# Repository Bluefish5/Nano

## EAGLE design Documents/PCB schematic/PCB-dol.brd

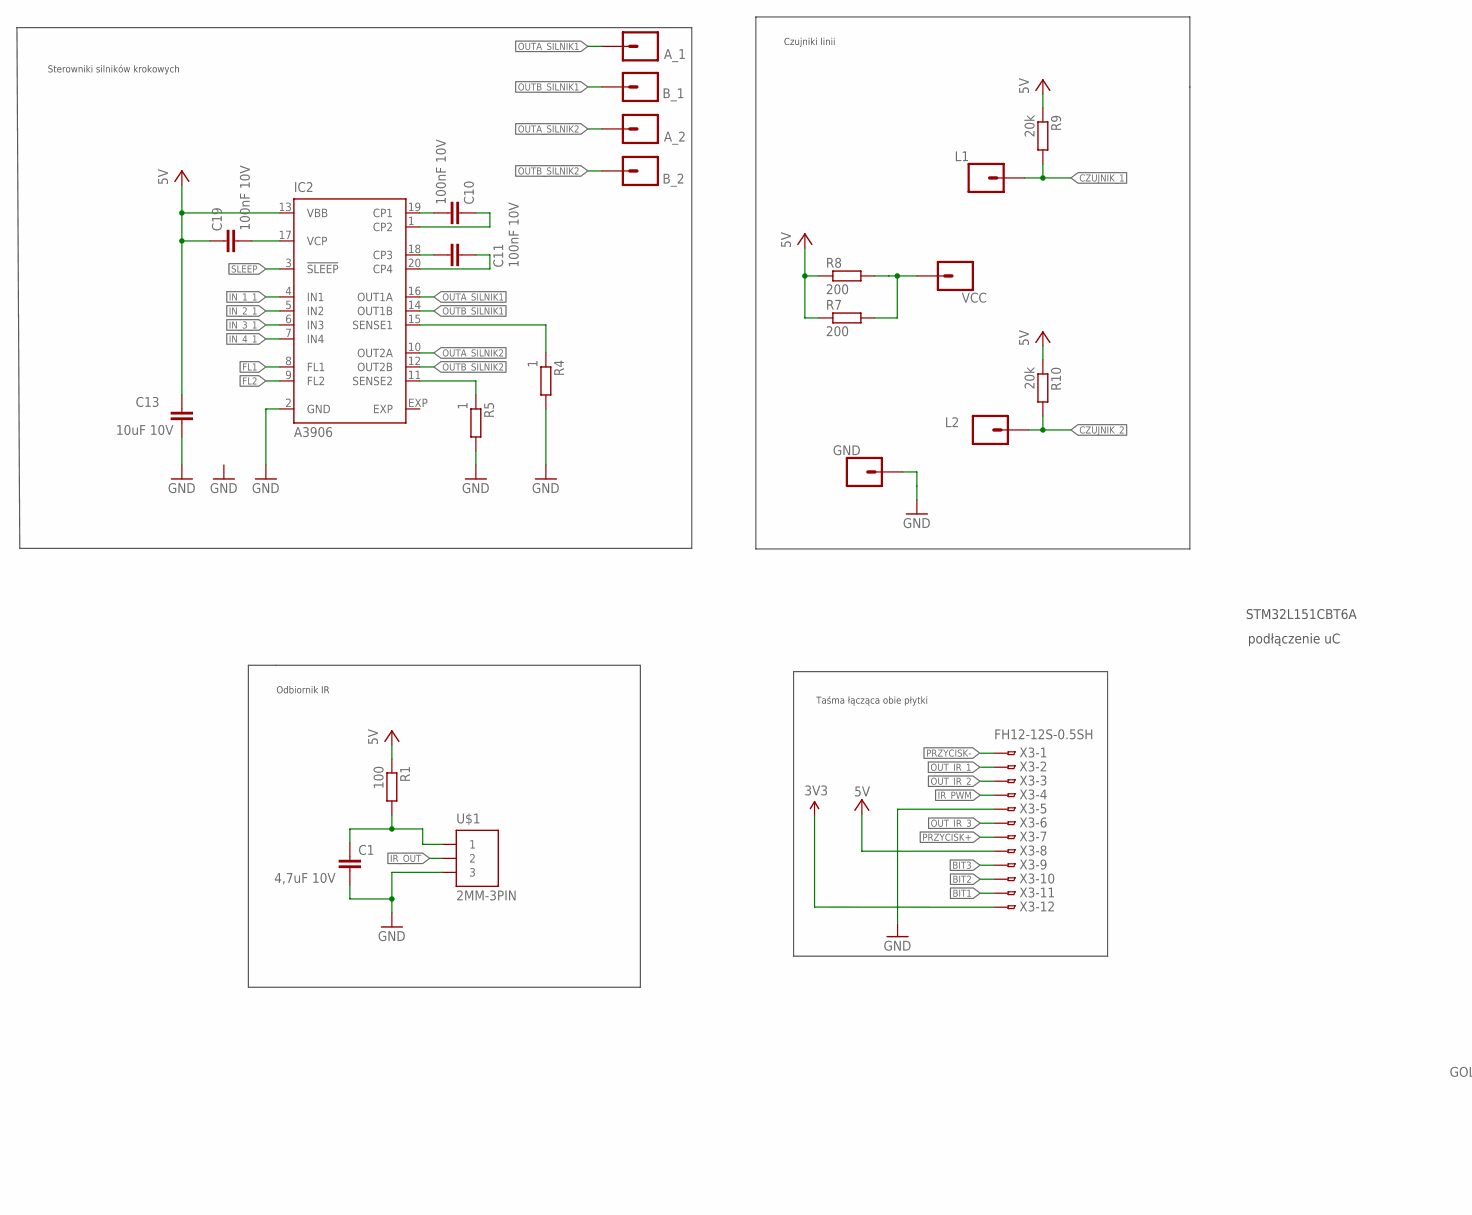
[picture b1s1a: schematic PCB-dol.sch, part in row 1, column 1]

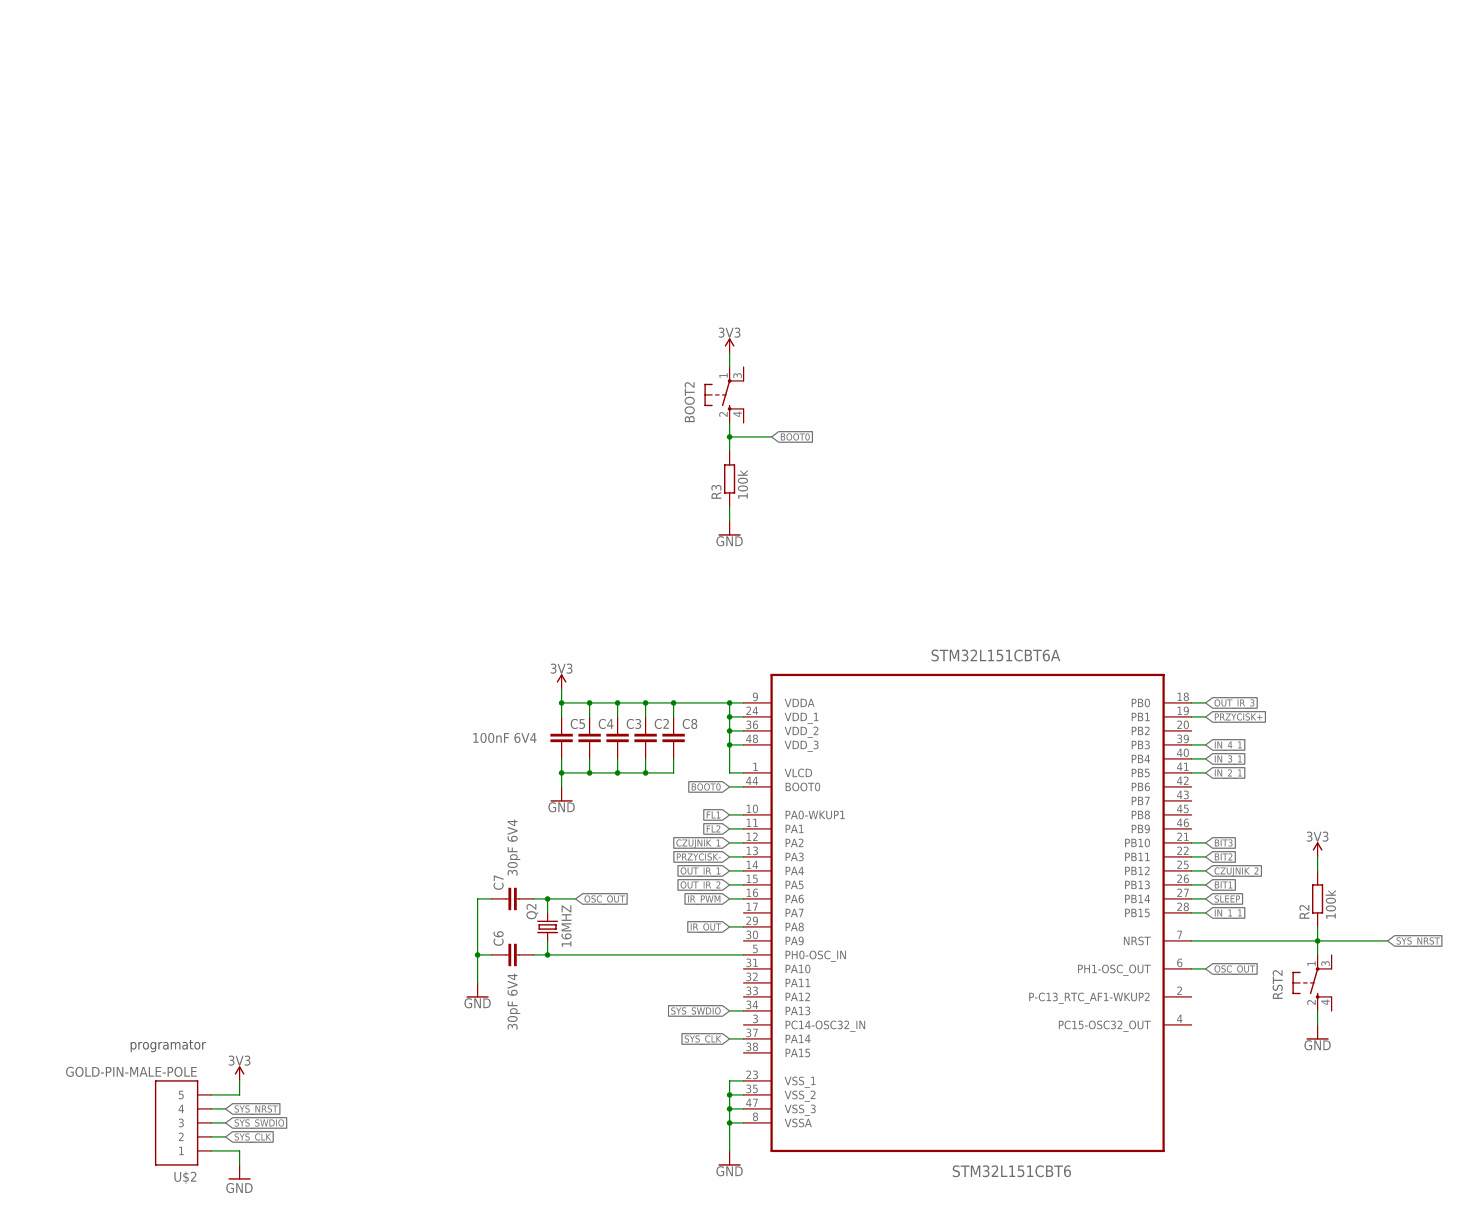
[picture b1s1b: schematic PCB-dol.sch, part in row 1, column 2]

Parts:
A_1, A_2: CONN_01PTH_NO_SILK_KIT; 1X01NS_KIT
BOOT2: SPST_TACT-KMR2; KMR2
B_1, B_2: CONN_01PTH_NO_SILK_KIT; 1X01NS_KIT
C1: 4,7uF 10V; C0402
C2, C3, C4, C5, C8: 100nF 6V4; C0402
C6, C7: 30pF 6V4; C0402
C10, C11, C19: 100nF 10V; C0402
C13: 10uF 10V; C0402
GND: CONN_01PTH_NO_SILK_KIT; 1X01NS_KIT
IC2: A3906; QFN20
L1, L2: CONN_01PTH_NO_SILK_KIT; 1X01NS_KIT
Q2: 16MHZ; 3.2X2.5_KX-7
R1: 100; R0402
R2, R3: 100k; R0402
R4, R5: 1; R0402
R7, R8: 200; R0805
R9, R10: 20k; R0402
RST2: SPST_TACT-KMR2; KMR2
STM32L151CBT6A: STM32L151CBT6; QFP50P900X900X160-48N
U$1: 2MM-3PIN
U$2: GOLD-PIN-MALE-POLE; PIN5
VCC: CONN_01PTH_NO_SILK_KIT; 1X01NS_KIT
X3: FH12-12S-0.5SH

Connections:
3.3V: BOOT2.1, C2.1, C3.1, C4.1, C5.1, C8.1, R2.2, STM32L151CBT6A.1 (VLCD), STM32L151CBT6A.9 (VDDA), STM32L151CBT6A.24 (VDD_1), STM32L151CBT6A.36 (VDD_2), STM32L151CBT6A.48 (VDD_3), U$2.P$5 (5), X3.12
BIT1: STM32L151CBT6A.26 (PB13), X3.11
BIT2: STM32L151CBT6A.22 (PB11), X3.10
BIT3: STM32L151CBT6A.21 (PB10), X3.9
BOOT0: BOOT2.2 (S), R3.2, STM32L151CBT6A.44 (BOOT0)
CZUJNIK_1: L1.1, R9.2, STM32L151CBT6A.12 (PA2)
CZUJNIK_2: L2.1, R10.2, STM32L151CBT6A.25 (PB12)
FL1: IC2.8 (FL1), STM32L151CBT6A.10 (PA0-WKUP1)
FL2: IC2.9 (FL2), STM32L151CBT6A.11 (PA1)
GND: C1.2, C2.2, C3.2, C4.2, C5.2, C6.1, C7.1, C8.2, C13.1, GND.1, IC2.2 (GND), R3.1, R4.2, R5.2, RST2.2 (S), STM32L151CBT6A.8 (VSSA), STM32L151CBT6A.23 (VSS_1), STM32L151CBT6A.35 (VSS_2), STM32L151CBT6A.47 (VSS_3), U$1.P$3 (3), U$2.P$1 (1), X3.5
IN_1_1: IC2.4 (IN1), STM32L151CBT6A.28 (PB15)
IN_2_1: IC2.5 (IN2), STM32L151CBT6A.41 (PB5)
IN_3_1: IC2.6 (IN3), STM32L151CBT6A.40 (PB4)
IN_4_1: IC2.7 (IN4), STM32L151CBT6A.39 (PB3)
IR_OUT: STM32L151CBT6A.29 (PA8), U$1.P$2 (2)
IR_PWM: STM32L151CBT6A.16 (PA6), X3.4
unnamed: C6.2, Q2.1, STM32L151CBT6A.5 (PH0-OSC_IN)
unnamed: C1.1, R1.2, U$1.P$1 (1)
unnamed: IC2.11 (SENSE2), R5.1
unnamed: C10.2, IC2.1 (CP2)
unnamed: C11.2, IC2.20 (CP4)
unnamed: IC2.15 (SENSE1), R4.1
unnamed: R7.2, R8.2, VCC.1
unnamed: C10.1, IC2.19 (CP1)
unnamed: C11.1, IC2.18 (CP3)
unnamed: C19.1, IC2.17 (VCP)
OSC_OUT: C7.2, Q2.3 (2), STM32L151CBT6A.6 (PH1-OSC_OUT)
OUTA_SILNIK1: A_1.1, IC2.16 (OUT1A)
OUTA_SILNIK2: A_2.1, IC2.10 (OUT2A)
OUTB_SILNIK1: B_1.1, IC2.14 (OUT1B)
OUTB_SILNIK2: B_2.1, IC2.12 (OUT2B)
OUT_IR_1: STM32L151CBT6A.14 (PA4), X3.2
OUT_IR_2: STM32L151CBT6A.15 (PA5), X3.3
OUT_IR_3: STM32L151CBT6A.18 (PB0), X3.6
PRZYCISK+: STM32L151CBT6A.19 (PB1), X3.7
PRZYCISK-: STM32L151CBT6A.13 (PA3), X3.1
SLEEP: IC2.3 (!SLEEP), STM32L151CBT6A.27 (PB14)
SYS_CLK: STM32L151CBT6A.37 (PA14), U$2.P$2 (2)
SYS_NRST: R2.1, RST2.1, STM32L151CBT6A.7 (NRST), U$2.P$4 (4)
SYS_SWDIO: STM32L151CBT6A.34 (PA13), U$2.P$3 (3)
VCC: C13.2, C19.2, IC2.13 (VBB), R1.1, R7.1, R8.1, R9.1, R10.1, X3.8

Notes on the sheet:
Sterowniki silników krokowych
programator
podłączenie uC
Odbiornik IR
Czujniki linii
Taśma łącząca obie płytki
STM32L151CBT6A

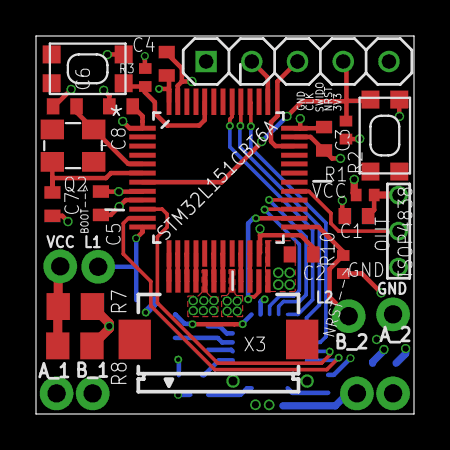
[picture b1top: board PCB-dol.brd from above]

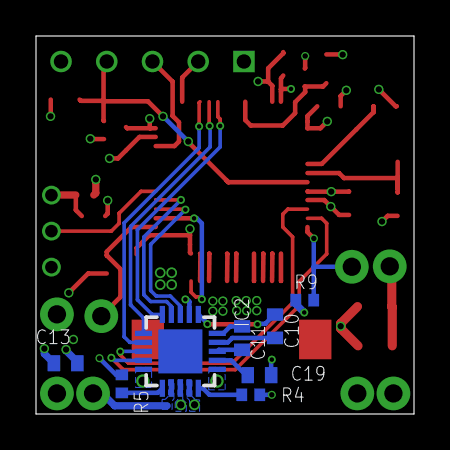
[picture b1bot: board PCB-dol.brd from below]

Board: 4 copper layers, 21.0 x 21.0 mm, 37 parts (8 on the bottom side), 41 nets.

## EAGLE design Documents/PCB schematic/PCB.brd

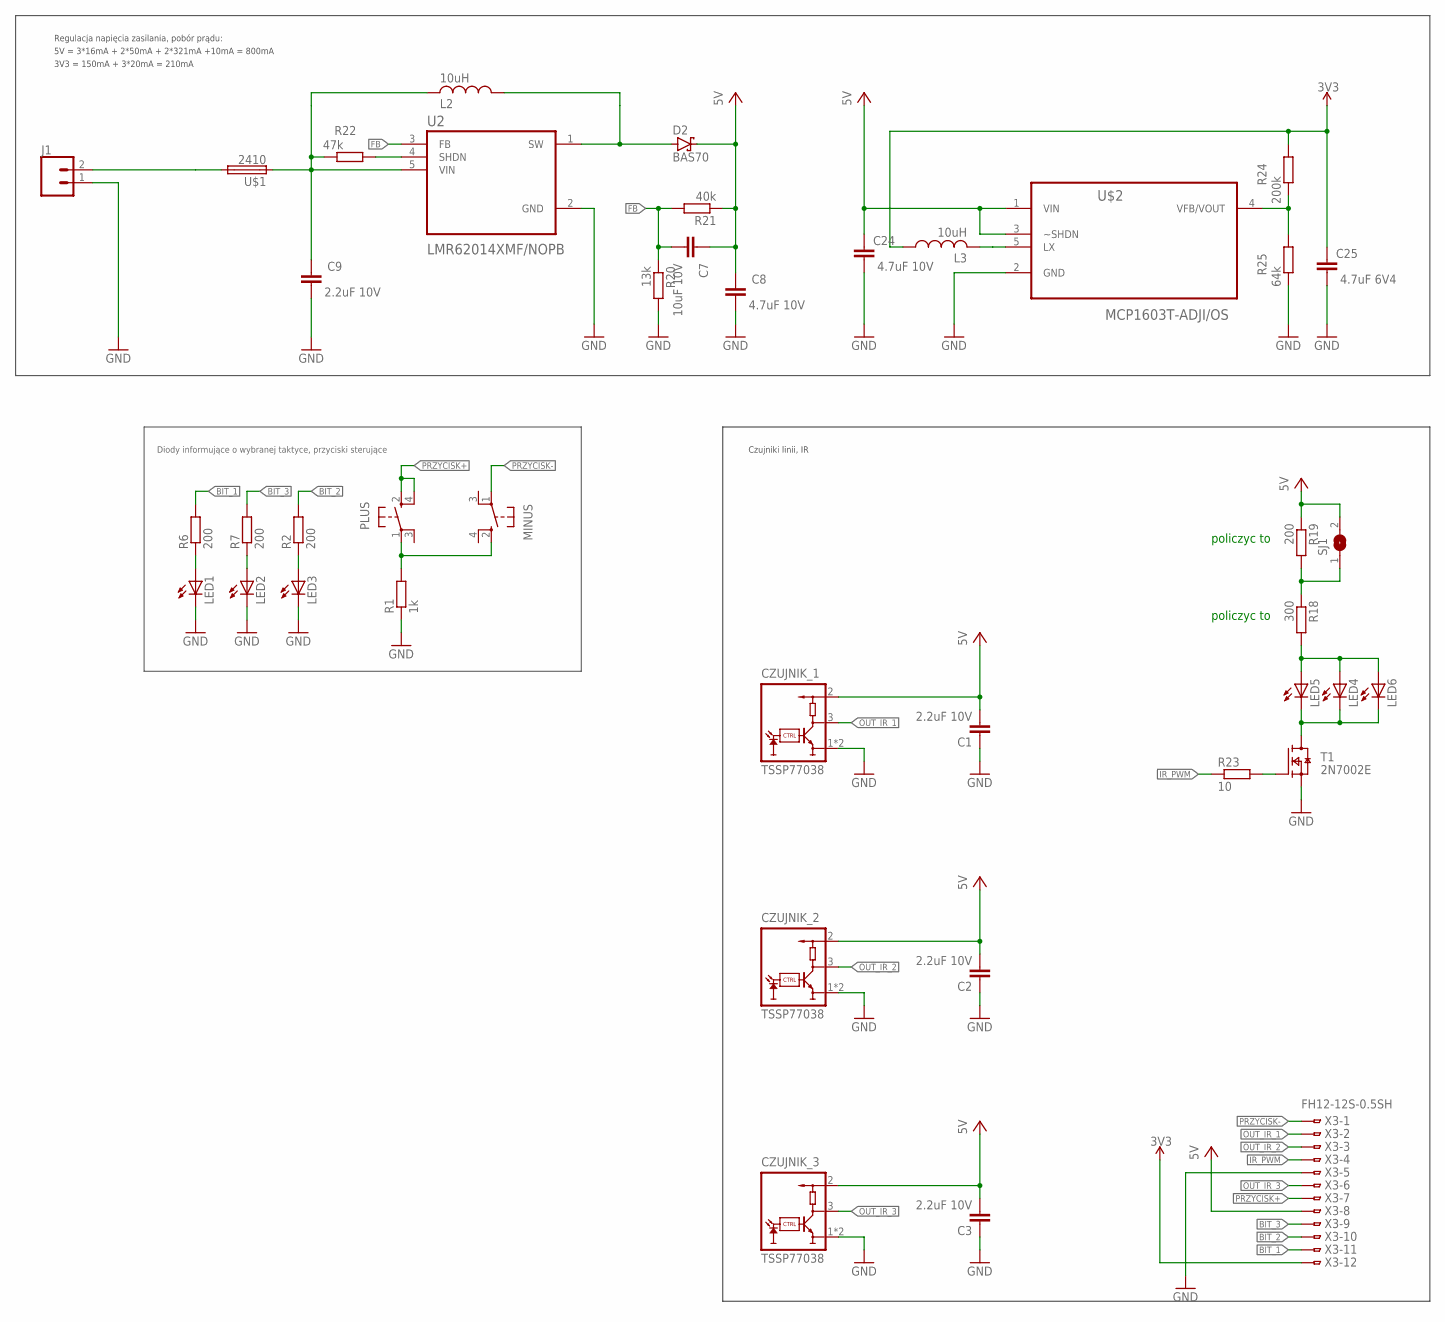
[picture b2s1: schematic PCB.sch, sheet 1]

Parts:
C1, C2, C3, C9: 2.2uF 10V; C0402
C7: 10uF 10V; C0402
C8, C24: 4.7uF 10V; C0402
C25: 4.7uF 6V4; C0402
CZUJNIK_1, CZUJNIK_2, CZUJNIK_3: TSSP77038
D2: BAS70; SOT23
J1: CONN_02POLAR_LOCK; MOLEX-1X2_LOCK
L2: 10uH; DJNR5020
L3: 10uH; L1812
LED1, LED2, LED3: LEDCHIP-LED0603; CHIP-LED0603
LED4, LED5, LED6: LED3MM
MINUS: SPST_TACT-KMR2; KMR2
PLUS: SPST_TACT-KMR2; KMR2
R1: 1k; R0402
R2, R6, R7: 200; R0805
R18: 300; R0402
R19: 200; R0402
R20: 13k; R0402
R21: 40k; R0402
R22: 47k; R0402
R23: 10; R0402
R24: 200k; R0402
R25: 64k; R0402
SJ1: SJ
T1: 2N7002E; SOT23
U2: LMR62014XMF/NOPB; SOT95P280X145-5N
U$1: 2410
U$2: MCP1603T-ADJI/OS; SOT95P280X110-5N
X3: FH12-12S-0.5SH

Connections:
3.3V: C25.2, L3.1, R24.1, X3.12
BIT_1: R6.2, X3.11
BIT_2: R2.2, X3.10
BIT_3: R7.2, X3.9
FB: C7.1, R20.1, R21.2, U2.3 (FB)
GND: C1.1, C2.1, C3.1, C8.1, C9.1, C24.1, C25.1, CZUJNIK_1.1 (GND), CZUJNIK_1.4 (GND), CZUJNIK_2.1 (GND), CZUJNIK_2.4 (GND), CZUJNIK_3.1 (GND), CZUJNIK_3.4 (GND), J1.1, LED1.C, LED2.C, LED3.C, R1.1, R20.2, R25.2, T1.2 (S), U2.2 (GND), U$2.2 (GND), X3.5
IR_PWM: R23.1, X3.4
unnamed: MINUS.2 (S), PLUS.1, R1.2
unnamed: LED2.A, R7.1
unnamed: LED3.A, R2.1
unnamed: LED1.A, R6.1
unnamed: C1.2, CZUJNIK_1.2 (VS)
unnamed: C3.2, CZUJNIK_3.2 (VS)
unnamed: C2.2, CZUJNIK_2.2 (VS)
unnamed: LED4.K (C), LED5.K (C), LED6.K (C), T1.3 (D)
unnamed: D2.1 (A), L2.P$1 (1), U2.1 (SW)
unnamed: R18.1, R19.2, SJ1.1
unnamed: LED4.A, LED5.A, LED6.A, R18.2
unnamed: R22.1, U2.4 (SHDN)
unnamed: J1.2, U$1.2
unnamed: C9.2, L2.P$2 (2), R22.2, U2.5 (VIN), U$1.1
unnamed: R23.2, T1.1 (G)
unnamed: L3.2, U$2.5 (LX)
unnamed: R24.2, R25.1, U$2.4 (VFB/VOUT)
OUT_IR_1: CZUJNIK_1.3 (OUT), X3.2
OUT_IR_2: CZUJNIK_2.3 (OUT), X3.3
OUT_IR_3: CZUJNIK_3.3 (OUT), X3.6
PRZYCISK+: PLUS.2 (S), PLUS.4 (S1), X3.7
PRZYCISK-: MINUS.1, X3.1
VCC: C7.2, C8.2, C24.2, D2.3 (C), R19.1, R21.1, SJ1.2, U$2.1 (VIN), U$2.3 (~SHDN), X3.8

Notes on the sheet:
Diody informujące o wybranej taktyce, przyciski sterujące
policzyc to
3V3 = 150mA + 3*20mA = 210mA
5V = 3*16mA + 2*50mA + 2*321mA +10mA = 800mA
Regulacja napięcia zasilania, pobór prądu:
Czujniki linii, IR

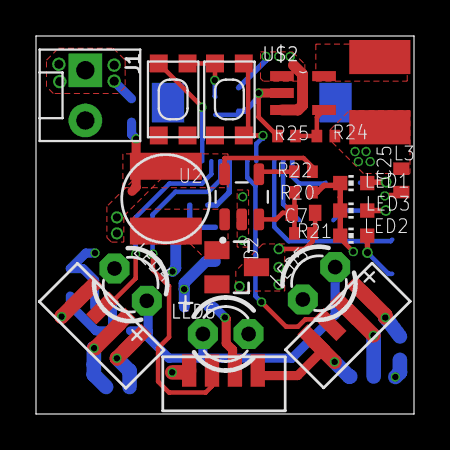
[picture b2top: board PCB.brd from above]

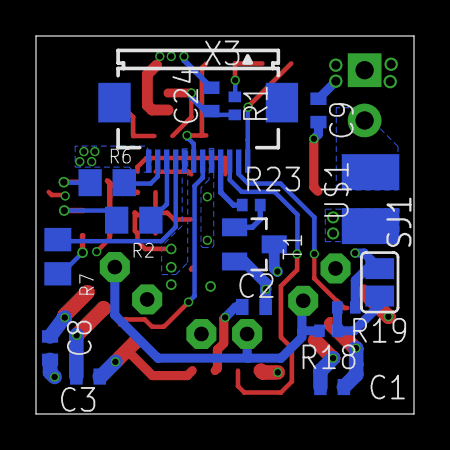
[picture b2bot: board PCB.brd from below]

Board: 4 copper layers, 21.0 x 21.0 mm, 41 parts (17 on the bottom side), 30 nets.

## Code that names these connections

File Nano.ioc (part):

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Mcu.Name=STM32F030C6Tx
Mcu.Package=LQFP48
Mcu.UserName=STM32F030C6Tx
PA0.GPIOParameters=PinState,GPIO_PuPd,GPIO_Label
PA0.GPIO_Label=H_BRIDGE_FL_1
PA0.GPIO_PuPd=GPIO_PULLUP
PA0.PinState=GPIO_PIN_SET
PA0.Signal=GPIO_Output
PA1.GPIOParameters=PinState,GPIO_PuPd,GPIO_Label
PA1.GPIO_Label=H_BRIDGE_FL_2
PA1.GPIO_PuPd=GPIO_PULLUP
PA1.PinState=GPIO_PIN_SET
PA1.Signal=GPIO_Output
PA13.Mode=Serial_Wire
PA13.Signal=SYS_SWDIO
PA14.Mode=Serial_Wire
PA14.Signal=SYS_SWCLK
PA2.GPIOParameters=GPIO_Label
PA2.GPIO_Label=LINE_SENSOR_1
PA2.Signal=GPIO_Input
PA3.GPIOParameters=GPIO_PuPd,GPIO_Label
PA3.GPIO_Label=BUTTON_2
PA3.GPIO_PuPd=GPIO_PULLUP
PA3.Signal=GPIO_Input
PA4.GPIOParameters=GPIO_Label
PA4.GPIO_Label=SENSOR_1
PA4.Mode=IN4
PA4.Signal=ADC_IN4
PA5.GPIOParameters=GPIO_Label
PA5.GPIO_Label=SENSOR_2
PA5.Mode=IN5
PA5.Signal=ADC_IN5
PA6.GPIOParameters=GPIO_Label
PA6.GPIO_Label=IR_PWM
PA6.Signal=GPIO_Output
PA8.GPIOParameters=GPIO_Label,GPIO_ModeDefaultEXTI
PA8.GPIO_Label=STARTER
PA8.GPIO_ModeDefaultEXTI=GPIO_MODE_IT_FALLING
PA8.Signal=GPXTI8
PB0.GPIOParameters=GPIO_Label
PB0.GPIO_Label=SENSOR_3
PB0.Mode=IN8
PB0.Signal=ADC_IN8
PB1.GPIOParameters=GPIO_PuPd,GPIO_Label
PB1.GPIO_Label=BUTTON_1
PB1.GPIO_PuPd=GPIO_PULLUP
PB1.Signal=GPIO_Input
PB10.GPIOParameters=GPIO_Label
PB10.GPIO_Label=LED_3
PB10.Signal=GPIO_Output
PB11.GPIOParameters=GPIO_Label
PB11.GPIO_Label=LED_2
PB11.Signal=GPIO_Output
PB12.GPIOParameters=GPIO_Label
PB12.GPIO_Label=LINE_SENSOR_2
PB12.Signal=GPIO_Input
PB13.GPIOParameters=GPIO_Label
PB13.GPIO_Label=LED_1
PB13.Signal=GPIO_Output
PB14.GPIOParameters=PinState,GPIO_PuPd,GPIO_Label
PB14.GPIO_Label=H_BRIDGE_SLEEP
PB14.GPIO_PuPd=GPIO_PULLDOWN
PB14.PinState=GPIO_PIN_SET
PB14.Signal=GPIO_Output
PB15.GPIOParameters=GPIO_Speed,GPIO_Label
PB15.GPIO_Label=H_BRIDGE_IN_1
PB15.GPIO_Speed=GPIO_SPEED_FREQ_HIGH
PB15.Signal=GPIO_Output
PB3.GPIOParameters=GPIO_Speed,GPIO_Label
PB3.GPIO_Label=H_BRIDGE_IN_4
PB3.GPIO_Speed=GPIO_SPEED_FREQ_HIGH
PB3.Signal=GPIO_Output
PB4.GPIOParameters=GPIO_Speed,GPIO_Label
PB4.GPIO_Label=H_BRIDGE_IN_3
PB4.GPIO_Speed=GPIO_SPEED_FREQ_HIGH
PB4.Signal=GPIO_Output
PB5.GPIOParameters=GPIO_Speed,GPIO_Label
PB5.GPIO_Label=H_BRIDGE_IN_2
PB5.GPIO_Speed=GPIO_SPEED_FREQ_HIGH
PB5.Signal=GPIO_Output
PF0-OSC_IN.Mode=HSE-External-Oscillator
PF0-OSC_IN.Signal=RCC_OSC_IN
PF1-OSC_OUT.Mode=HSE-External-Oscillator
PF1-OSC_OUT.Signal=RCC_OSC_OUT
RCC.SYSCLKFreq_VALUE=16000000
RCC.SYSCLKSource=RCC_SYSCLKSOURCE_PLLCLK
board=custom

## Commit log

2022-12-02 Innit 🛠
2022-12-02 Piwnica - 02.12.22
2022-12-05 First working program
2022-12-05 Bugfix
2022-12-06 Final commit

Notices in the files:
parts and their libraries:
crystal-geyer_V1_0: Copyright: Geyer-Electronic
SparkFun-Connectors: Licensing: Creative Commons ShareAlike 4.0 International - https://creativecommons.org/licenses/by-sa/4.0
